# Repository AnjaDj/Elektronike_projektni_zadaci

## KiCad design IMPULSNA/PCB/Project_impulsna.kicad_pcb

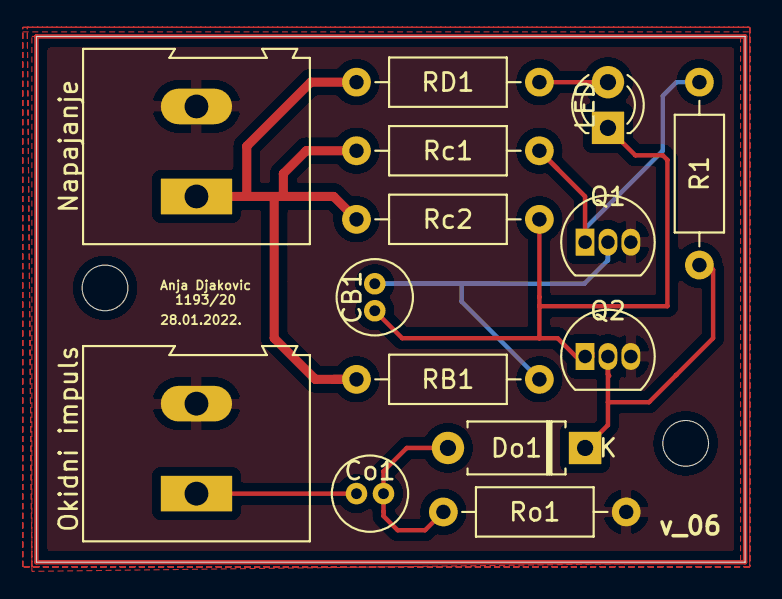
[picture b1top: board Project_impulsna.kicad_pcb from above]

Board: 2 copper layers, 39.4 x 29.2 mm, 14 parts (0 on the bottom side), 9 nets.

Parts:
CB1: 33.2uF; C_Radial_D4.0mm_H5.0mm_P1.50mm
Co1: 1uF; C_Radial_D4.0mm_H5.0mm_P1.50mm
Do1: D; D_A-405_P7.62mm_Horizontal
LED: RED; LED_D3.0mm
Napajanje: Napajanje; TerminalBlock_Altech_AK300-2_P5.00mm
Okidni impuls: Okidni impuls; TerminalBlock_Altech_AK300-2_P5.00mm
Q1, Q2: BC547; TO-92_Inline
R1: 4k; R_Axial_DIN0207_L6.3mm_D2.5mm_P10.16mm_Horizontal
RB1: 4.3k; R_Axial_DIN0207_L6.3mm_D2.5mm_P10.16mm_Horizontal
RD1: 155k; R_Axial_DIN0207_L6.3mm_D2.5mm_P10.16mm_Horizontal
Rc1: 242; R_Axial_DIN0207_L6.3mm_D2.5mm_P10.16mm_Horizontal
Rc2: 2.42k; R_Axial_DIN0207_L6.3mm_D2.5mm_P10.16mm_Horizontal
Ro1: 100; R_Axial_DIN0207_L6.3mm_D2.5mm_P10.16mm_Horizontal

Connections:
GND: Napajanje.2, Okidni impuls.2, Q1.3, Q2.3, Ro1.2
unnamed: CB1.1, LED.1, Q2.1, Rc2.2
unnamed: CB1.2, Q1.2, RB1.2
unnamed: Co1.1, Okidni impuls.1
unnamed: Co1.2, Do1.2, Ro1.1
unnamed: LED.2, RD1.2
unnamed: Do1.1, Q2.2, R1.1
unnamed: Q1.1, R1.2, Rc1.2
VCC: Napajanje.1, RB1.1, RD1.1, Rc1.1, Rc2.1

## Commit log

2023-12-07 Dodani fajlovi sa definicijom projektnih zadataka
2023-12-07 second commit
2024-08-02 Added README.md file
2024-08-02 Dodan materijal sa auditornih i laboratorijskih vjezbi
